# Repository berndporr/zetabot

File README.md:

# The Zeta-bot

What is the Zeta-Bot?

The Zeta-Bot is an open-source robot platform that uses the:

 - Raspberry PI 5 + active cooling fan
 - [Parallax's Continuous Rotation Servo Motors](https://www.parallax.com/product/parallax-continuous-rotation-servo/),
 - [C1 LIDAR](https://www.slamtec.com/en/c1),
 - [OV9281 global shutter camera](https://www.inno-maker.com/product/cam-mipi9281raw-v2/)
 - [LSM6DSOX Gyro/Accelerometer](https://github.com/berndporr/LSM6DSOX_RPi)
 - [a standard mobile phone 1700mAh power bank](https://uk.rs-online.com/web/p/power-banks/2498449),
 - [Pimoroni NVMe Base M.2 PCIe](https://shop.pimoroni.com/products/nvme-base?variant=41219587178579)

This is an ongoing project to provide the hardware 
for research in robotic planning.

## Hardware

The KiCad design files and BOM are in [hardware](hardware).

## Software

 - Motor control libraries: [wheeleddrive](wheeleddrive).
 - Camera driver: https://github.com/berndporr/libcamera2opencv with a demo to display the camera image.
 - LIDAR driver: https://github.com/berndporr/c1lidar
 - [LSM6DSOX Gyro/Accelerometer](https://github.com/berndporr/LSM6DSOX_RPi)

## Credits

 - (c) 2026, Bernd Porr, mail@berndporr.me.uk
 - (c) 2025, Saleh AlMulla
 - (c) 2025, Yixuan Zha

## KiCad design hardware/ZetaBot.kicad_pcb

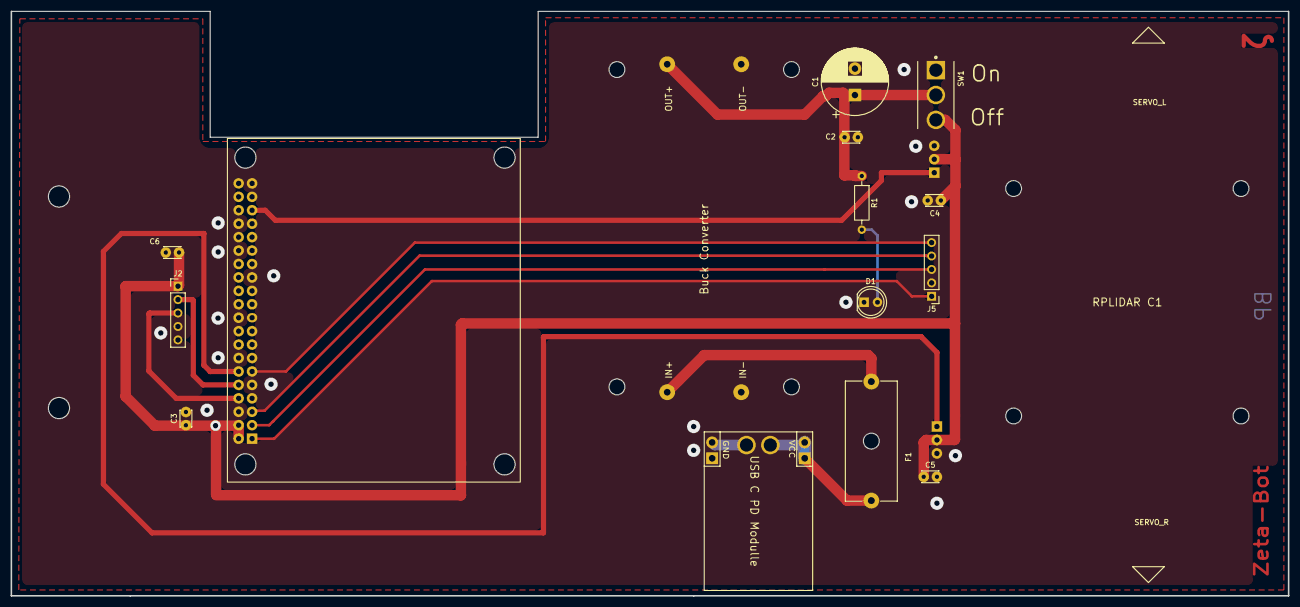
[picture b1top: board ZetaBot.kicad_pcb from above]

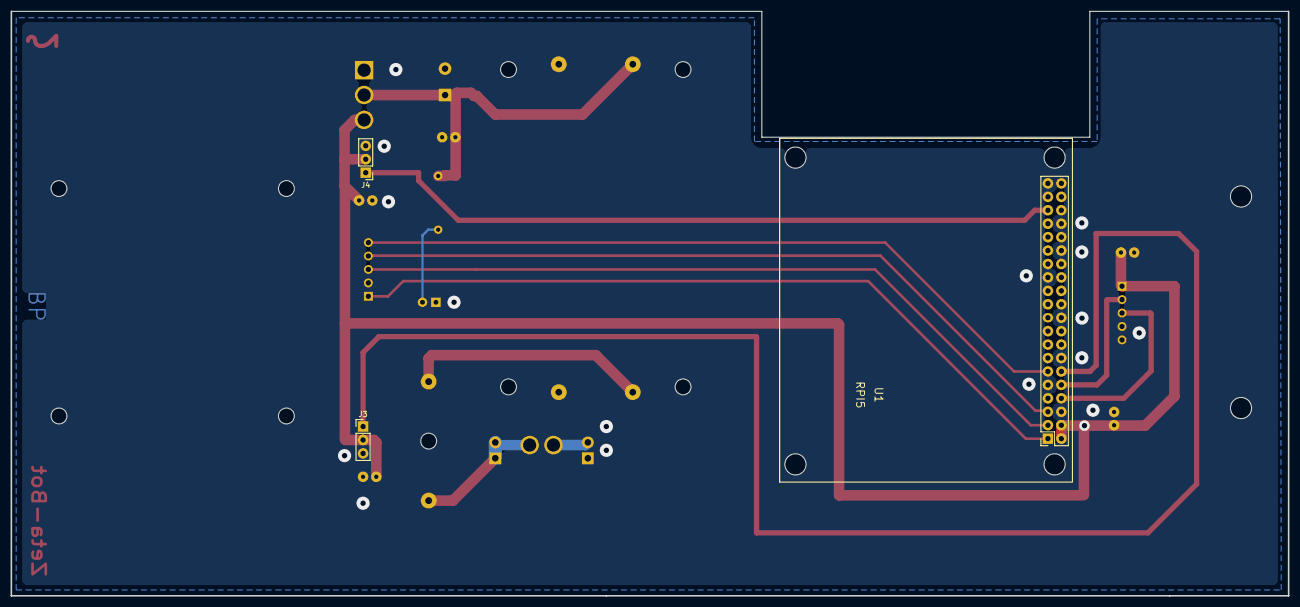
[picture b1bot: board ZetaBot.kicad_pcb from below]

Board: 2 copper layers, 241.5 x 110.5 mm, 18 parts (3 on the bottom side), 14 nets.

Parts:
C1: 2200uF; CP_Radial_D12.5mm_P5.00mm
C2, C3, C4, C5, C6: 1uF; C_Disc_D3.0mm_W2.0mm_P2.50mm
D1: LED; LED_D5.0mm_Clear
F1: Fuse; Fuseholder_Cylinder-5x20mm_Schurter_0031_8201_Horizontal_Op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
J1: USB C PD Modulle; USB_C
J2: Conn_01x05; PinHeader_1x05_P2.54mm_Vertical
J3: MOTOR_R; PinHeader_1x03_P2.54mm_Vertical
J4: MOTOR_L; PinHeader_1x03_P2.54mm_Vertical
J5: LSM6DSOX; PinHeader_1x05_P2.54mm_Vertical
R1: 330R; R_Axial_DIN0207_L6.3mm_D2.5mm_P10.16mm_Horizontal
SW1: SW_SPDT; TE_4-1825136-5
U1: RPLIDAR C1
U1#2: RPI5
U2: Buck Converter; BUCK_CONV

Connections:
+5V: C3.1, C4.1, C5.1, C6.1, J2.1, J3.2, J4.2, SW1.3 (C), U1#2.2 (5V1), U1#2.4 (5V2)
+9V: F1.1, U2.1 (IN+)
GND: C1.2, C2.2, C3.2, C4.2, C5.2, C6.2, D1.1 (K), J1.2 (GND), J1.4 (GND), J2.4, J3.3, J4.3, J5.2, U1#2.6 (GND1), U1#2.9 (GND8), U1#2.14 (GND2), U1#2.20 (GND3), U1#2.25 (GND7), U1#2.30 (GND4), U1#2.34 (GND5), U1#2.39 (GND6), U2.2 (IN-), U2.4 (OUT-)
LIDAR_RX: J2.3, U1#2.8 (GPIO14_UART/TX)
LIDAR_TX: J2.2, U1#2.10 (GPIO15_UART/RX)
unnamed: D1.2 (A), R1.2
unnamed: F1.2, J1.1 (VCC), J1.3 (VCC)
unnamed: J5.1, U1#2.1 (3.3V)
unnamed: J5.3, U1#2.3 (GPIO02_I2C1/SDA)
unnamed: J5.4, U1#2.5 (GPIO03_I2C1/SCL)
unnamed: J5.5, U1#2.11 (GPIO17)
unnamed: C1.1, C2.1, R1.1, SW1.2 (B), U2.3 (OUT+)
PWM_L: J4.1, U1#2.35 (GPIO19_PWM0/CHAN2)
PWM_R: J3.1, U1#2.12 (GPIO18_PWM0/CHAN2)

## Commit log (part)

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2026-04-12 It's now the Zeta-bot
2026-04-12 Fixed local library include
2026-04-12 Updated buck converter and re designed layout. Need to DRC.
2026-04-12 Got rid of the old photos.
2026-04-12 2nd revision. DRC passed.
2026-04-13 Added two holes for the caster ball.
2026-04-14 Updated the masks with the two drill holes
2026-04-14 Updated drill and gerber
2026-04-14 Added motor control
2026-04-14 Changed to zetabot
2026-04-14 Removed old refs
2026-04-14 On/Off was wrongly labelled
2026-04-15 Updated the nets of the motors (L-R) and the pin headers.
2026-04-15 Made it compatible to the deltabot
2026-04-15 Added basic info about the robot
2026-04-15 Added more info how to control the motors.
2026-04-23 Fixed defines to Zeta
2026-04-26 Added stereo camera application
2026-04-26 Added links
2026-04-26 Added info about the power bank.
2026-04-26 Fixed the stereo (again).
2026-04-26 Added info that it's C++
2026-04-27 Wire diameter corrected
2026-04-28 modified for c++ 17
2026-04-28 removed commented
2026-04-29 swapped motors
2026-04-29 endless swapping and changed sprintf for l wheel

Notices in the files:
hardware/ZetaBot.kicad_pcb:
GPL
